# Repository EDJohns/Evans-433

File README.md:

# Welcome to GitHub Desktop!

This is your README. READMEs are where you can communicate what your project is and how to use it.

Write your name on line 6, save it, and then head back to GitHub Desktop.
Evan Johns

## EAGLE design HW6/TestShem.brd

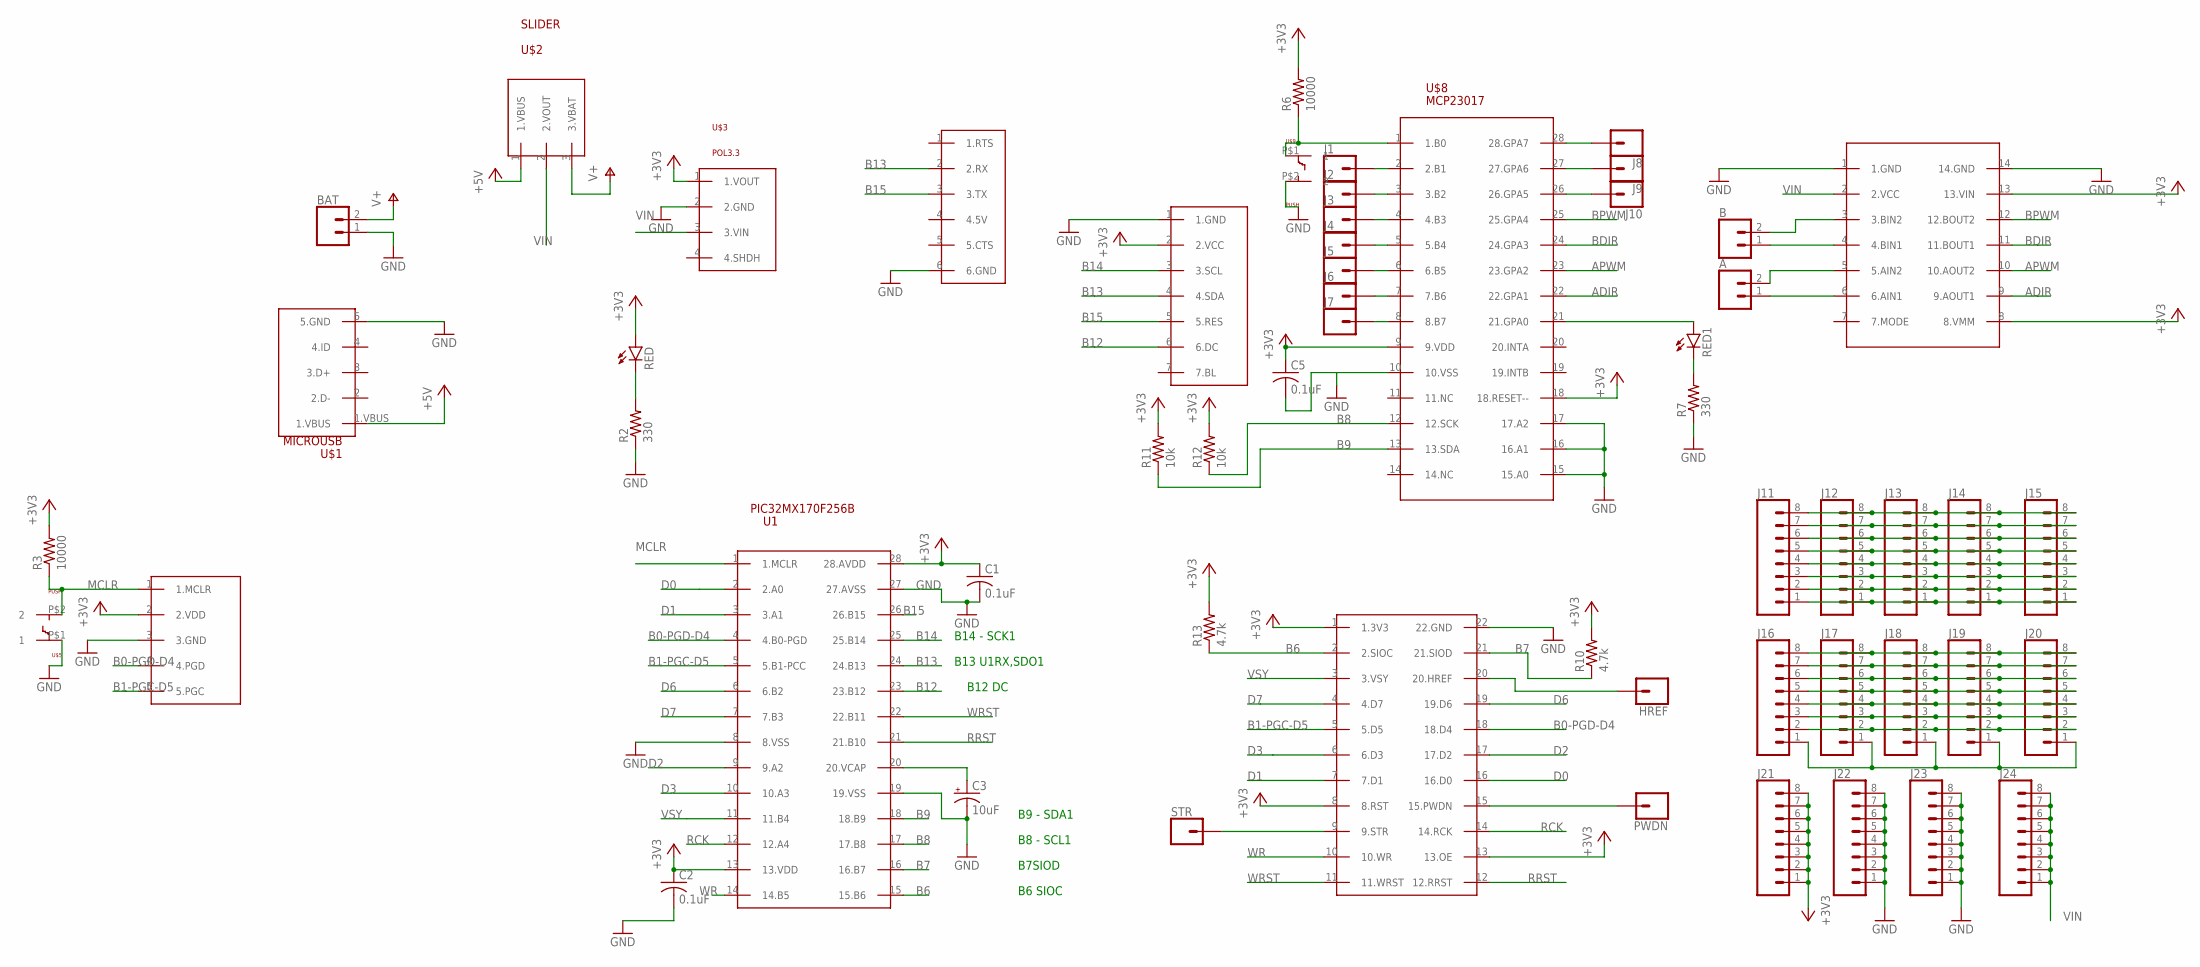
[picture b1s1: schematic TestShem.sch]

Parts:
A: CONN_02; 1X02
B: CONN_02; 1X02
BAT: CONN_02; 1X02
C1, C2, C5: 0.1uF; C025-030X050
C3: 10uF; B45181B
HREF: CONN_01; 1X01
J1, J2, J3, J4, J5, J6, J7, J8, J9, J10: CONN_01; 1X01
J11, J12, J13, J14, J15, J16, J17, J18, J19, J20, J21, J22, J23, J24: CONN_08"; 1X08
PWDN: CONN_01; 1X01
R2, R7: 330; 0207/10
R3, R6: 10000; 0207/10
R10, R13: 4.7k; 0207/10
R11, R12: 10k; 0207/10
RED, RED1: LED3MM
STR: CONN_01; 1X01
U1: PIC32MX170F256B; DIL28-3
U$1: MICROUSB
U$2: SLIDER
U$3: POL3.3; POLOLU3.3
U$4: SNAP; 1X05
U$5, U$9: PUSH
U$6: ADACP2104; 1X06V2
U$7: ST7789; 1X07
U$8: MCP23017; DIL28-3
U$10: POLOLUDRV8835V2; 1X07V2
U$11: OV7670CAMFIXED; 1X02CAM

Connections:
10.VSS: C5.2, U$8.10 (10.VSS)
+3V3: C1.1, C2.1, C5.1, J21.1, J21.2, J21.3, J21.4, J21.5, J21.6, J21.7, J21.8, R3.2, R6.2, R10.2, R11.2, R12.2, R13.2, RED.A, U1.13 (13.VDD), U1.28 (28.AVDD), U$3.1 (1.VOUT), U$4.2 (2.VDD), U$7.2 (2.VCC), U$8.9 (9.VDD), U$8.18 (18.RESET--), U$10.8 (8.VMM), U$10.13 (13.VIN), U$11.1 (1.3V3), U$11.8 (8.RST), U$11.13 (13.OE)
+5V: U$1.1.VBUS, U$2.1 (1.VBUS)
ADIR: U$8.22 (22.GPA1), U$10.9 (9.AOUT1)
APWM: U$8.23 (23.GPA2), U$10.10 (10.AOUT2)
B0-PGD-D4: U1.4 (4.B0-PGD), U$4.4 (4.PGD), U$11.18 (18.D4)
B1-PGC-D5: U1.5 (5.B1-PCC), U$4.5 (5.PGC), U$11.5 (5.D5)
B6: R13.1, U1.15 (15.B6), U$11.2 (2.SIOC)
B7: R10.1, U1.16 (16.B7), U$11.21 (21.SIOD)
B8: R12.1, U1.17 (17.B8), U$8.12 (12.SCK)
B9: R11.1, U1.18 (18.B9), U$8.13 (13.SDA)
B12: U1.23 (23.B12), U$7.6 (6.DC)
B13: U1.24 (24.B13), U$6.2 (2.RX), U$7.4 (4.SDA)
B14: U1.25 (25.B14), U$7.3 (3.SCL)
B15: U1.26 (26.B15), U$6.3 (3.TX), U$7.5 (5.RES)
BDIR: U$8.24 (24.GPA3), U$10.11 (11.BOUT1)
BPWM: U$8.25 (25.GPA4), U$10.12 (12.BOUT2)
D0: U1.2 (2.A0), U$11.16 (16.D0)
D1: U1.3 (3.A1), U$11.7 (7.D1)
D2: U1.9 (9.A2), U$11.17 (17.D2)
D3: U1.10 (10.A3), U$11.6 (6.D3)
D6: U1.6 (6.B2), U$11.19 (19.D6)
D7: U1.7 (7.B3), U$11.4 (4.D7)
GND: BAT.1, C1.2, C2.2, C3.-, J22.1, J22.2, J22.3, J22.4, J22.5, J22.6, J22.7, J22.8, J23.1, J23.2, J23.3, J23.4, J23.5, J23.6, J23.7, J23.8, R2.1, R7.1, U1.8 (8.VSS), U1.19 (19.VSS), U1.27 (27.AVSS), U$1.5 (5.GND), U$3.2 (2.GND), U$4.3 (3.GND), U$5.P$1 (1), U$6.6 (6.GND), U$7.1 (1.GND), U$8.15 (15.A0), U$8.16 (16.A1), U$8.17 (17.A2), U$9.P$2 (2), U$10.1 (1.GND), U$10.14 (14.GND), U$11.22 (22.GND)
MCLR: R3.1, U1.1 (1.MCLR), U$4.1 (1.MCLR), U$5.P$2 (2)
unnamed: R2.2, RED.K (C)
unnamed: R6.1, U$8.1 (1.B0), U$9.P$1 (1)
unnamed: RED1.A, U$8.21 (21.GPA0)
unnamed: C3.+, U1.20 (20.VCAP)
unnamed: R7.2, RED1.K (C)
unnamed: B.2, U$10.3 (3.BIN2)
unnamed: B.1, U$10.4 (4.BIN1)
unnamed: A.2, U$10.5 (5.AIN2)
unnamed: A.1, U$10.6 (6.AIN1)
unnamed: PWDN.1, U$11.15 (15.PWDN)
unnamed: HREF.1, U$11.20 (20.HREF)
unnamed: STR.1, U$11.9 (9.STR)
unnamed: J1.1, U$8.2 (2.B1)
unnamed: J2.1, U$8.3 (3.B2)
unnamed: J3.1, U$8.4 (4.B3)
unnamed: J4.1, U$8.5 (5.B4)
unnamed: J5.1, U$8.6 (6.B5)
unnamed: J6.1, U$8.7 (7.B6)
unnamed: J7.1, U$8.8 (8.B7)
unnamed: J8.1, U$8.28 (28.GPA7)
unnamed: J9.1, U$8.27 (27.GPA6)
unnamed: J10.1, U$8.26 (26.GPA5)
unnamed: J11.8, J12.8, J13.8, J14.8, J15.8
unnamed: J11.7, J12.7, J13.7, J14.7, J15.7
unnamed: J11.6, J12.6, J13.6, J14.6, J15.6
unnamed: J11.5, J12.5, J13.5, J14.5, J15.5
unnamed: J11.4, J12.4, J13.4, J14.4, J15.4
unnamed: J11.3, J12.3, J13.3, J14.3, J15.3
unnamed: J11.2, J12.2, J13.2, J14.2, J15.2
unnamed: J11.1, J12.1, J13.1, J14.1, J15.1
unnamed: J16.8, J17.8, J18.8, J19.8, J20.8
unnamed: J16.7, J17.7, J18.7, J19.7, J20.7
unnamed: J16.6, J17.6, J18.6, J19.6, J20.6
unnamed: J16.5, J17.5, J18.5, J19.5, J20.5
unnamed: J16.4, J17.4, J18.4, J19.4, J20.4
unnamed: J16.3, J17.3, J18.3, J19.3, J20.3
unnamed: J16.2, J17.2, J18.2, J19.2, J20.2
unnamed: J16.1, J17.1, J18.1, J19.1, J20.1
RCK: U1.12 (12.A4), U$11.14 (14.RCK)
RRST: U1.21 (21.B10), U$11.12 (12.RRST)
V+: BAT.2, U$2.3 (3.VBAT)
VIN: J24.1, J24.2, J24.3, J24.4, J24.5, J24.6, J24.7, J24.8, U$2.2 (2.VOUT), U$3.3 (3.VIN), U$10.2 (2.VCC)
VSY: U1.11 (11.B4), U$11.3 (3.VSY)
WR: U1.14 (14.B5), U$11.10 (10.WR)
WRST: U1.22 (22.B11), U$11.11 (11.WRST)

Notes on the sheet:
B14 - SCK1
B12 DC
B13 U1RX,SDO1
B9 - SDA1
B8 - SCL1
B7SIOD
B6 SIOC

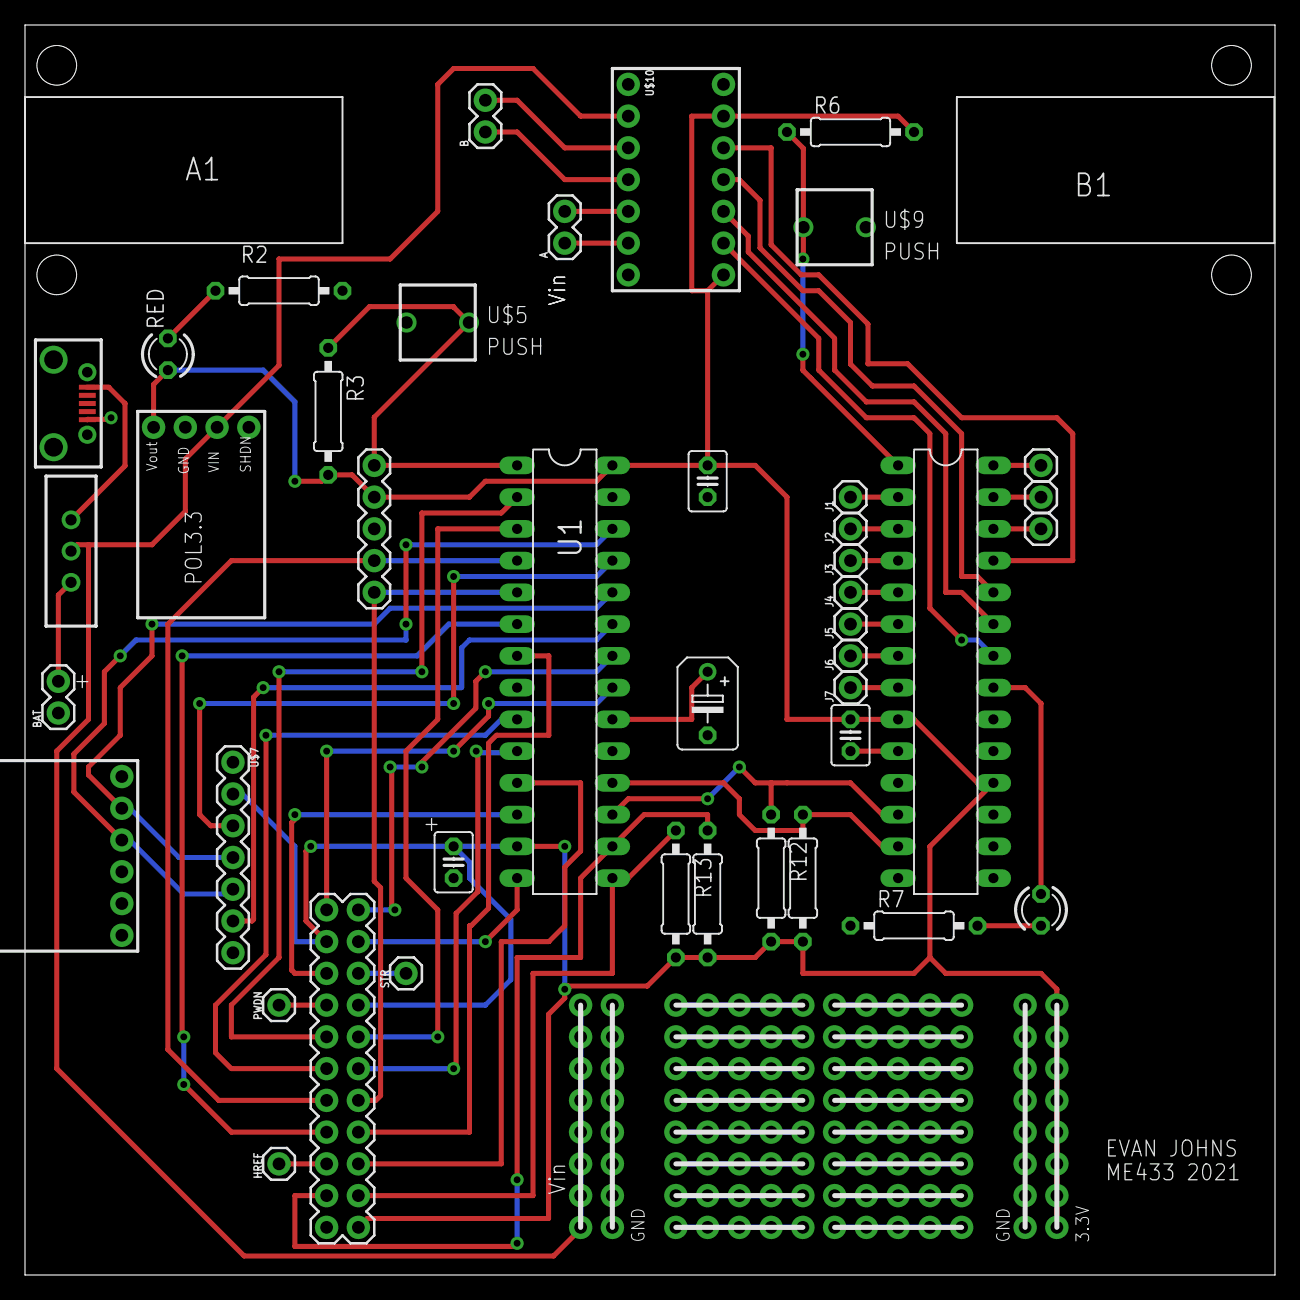
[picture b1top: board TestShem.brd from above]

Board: 2 copper layers, 100.0 x 100.0 mm, 56 parts (0 on the bottom side), 70 nets.

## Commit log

2021-04-05 Added My name
2021-04-06 name change
2021-04-12 added FIles
2021-04-18 HW5 info
2021-04-18 moved files
2021-04-19 Add demostration Video
2021-04-26 reogrinization
2021-04-26 reorginization
2021-04-28 Updated Code
2021-04-28 added video
2021-05-01 LED project adds
2021-05-10 Homework9
2021-05-10 Fixed Display errors
2021-05-13 Finished HW11
2021-05-16 HW 6 updates
2021-06-10 Added HW 12
2021-06-10 HW16
2021-06-11 HW update
2021-06-11 added printed photo
2021-11-18 ME 398 Code
2022-07-27 Added Evie's Reasearch
    Added Evie's Reasearch
